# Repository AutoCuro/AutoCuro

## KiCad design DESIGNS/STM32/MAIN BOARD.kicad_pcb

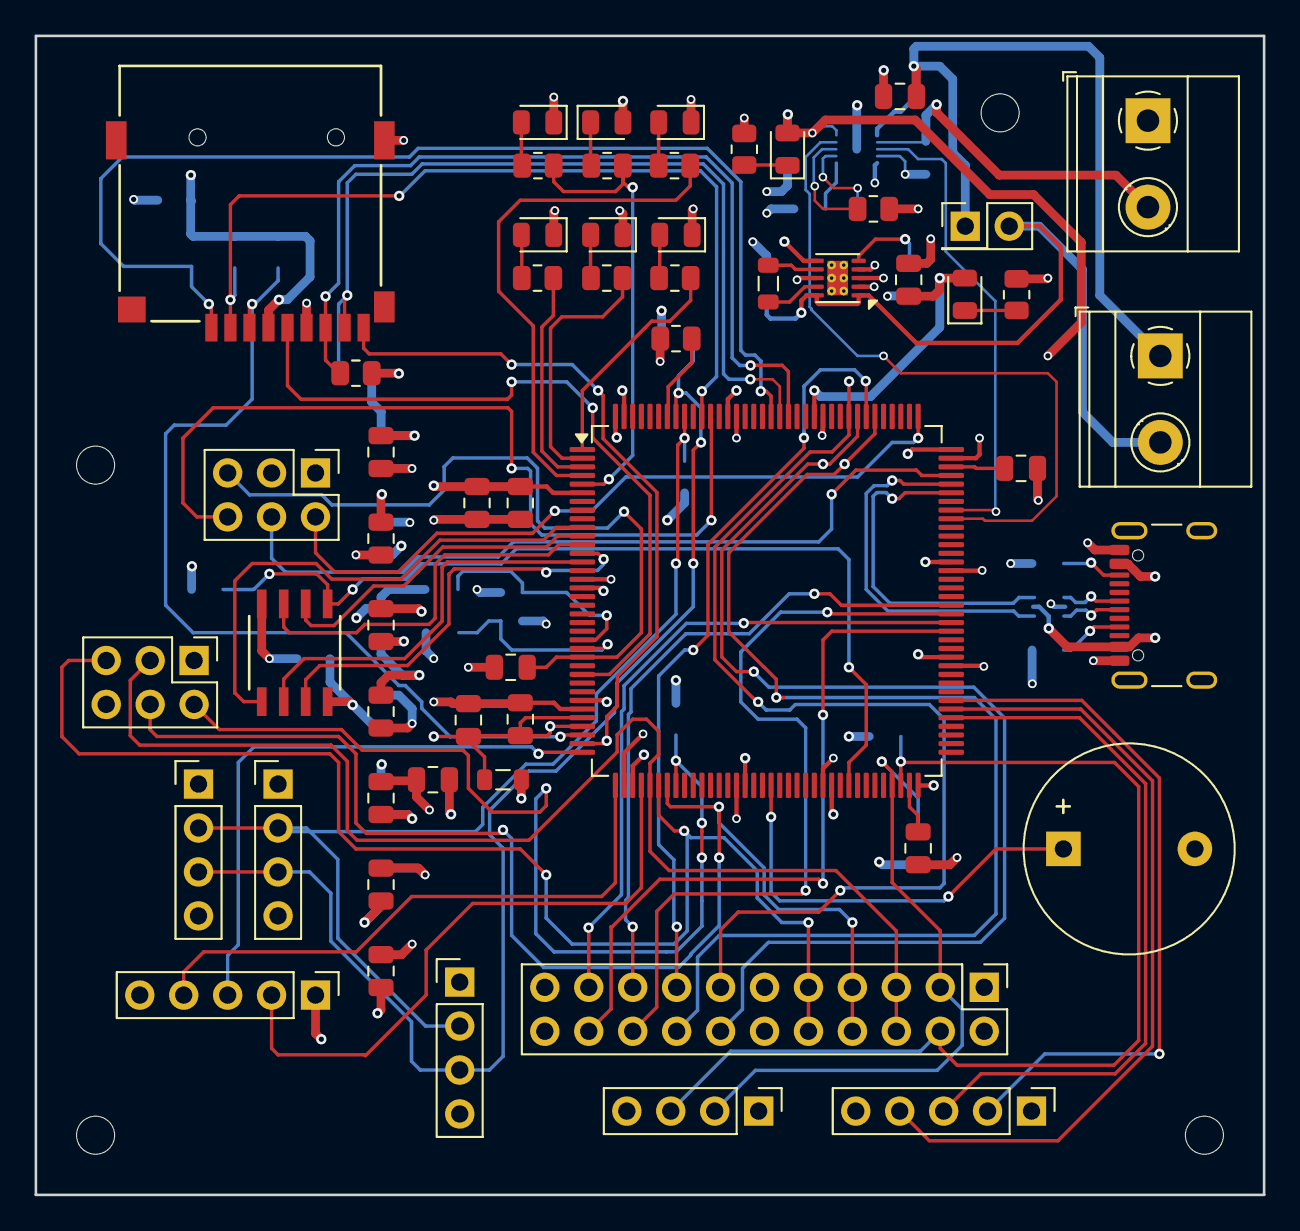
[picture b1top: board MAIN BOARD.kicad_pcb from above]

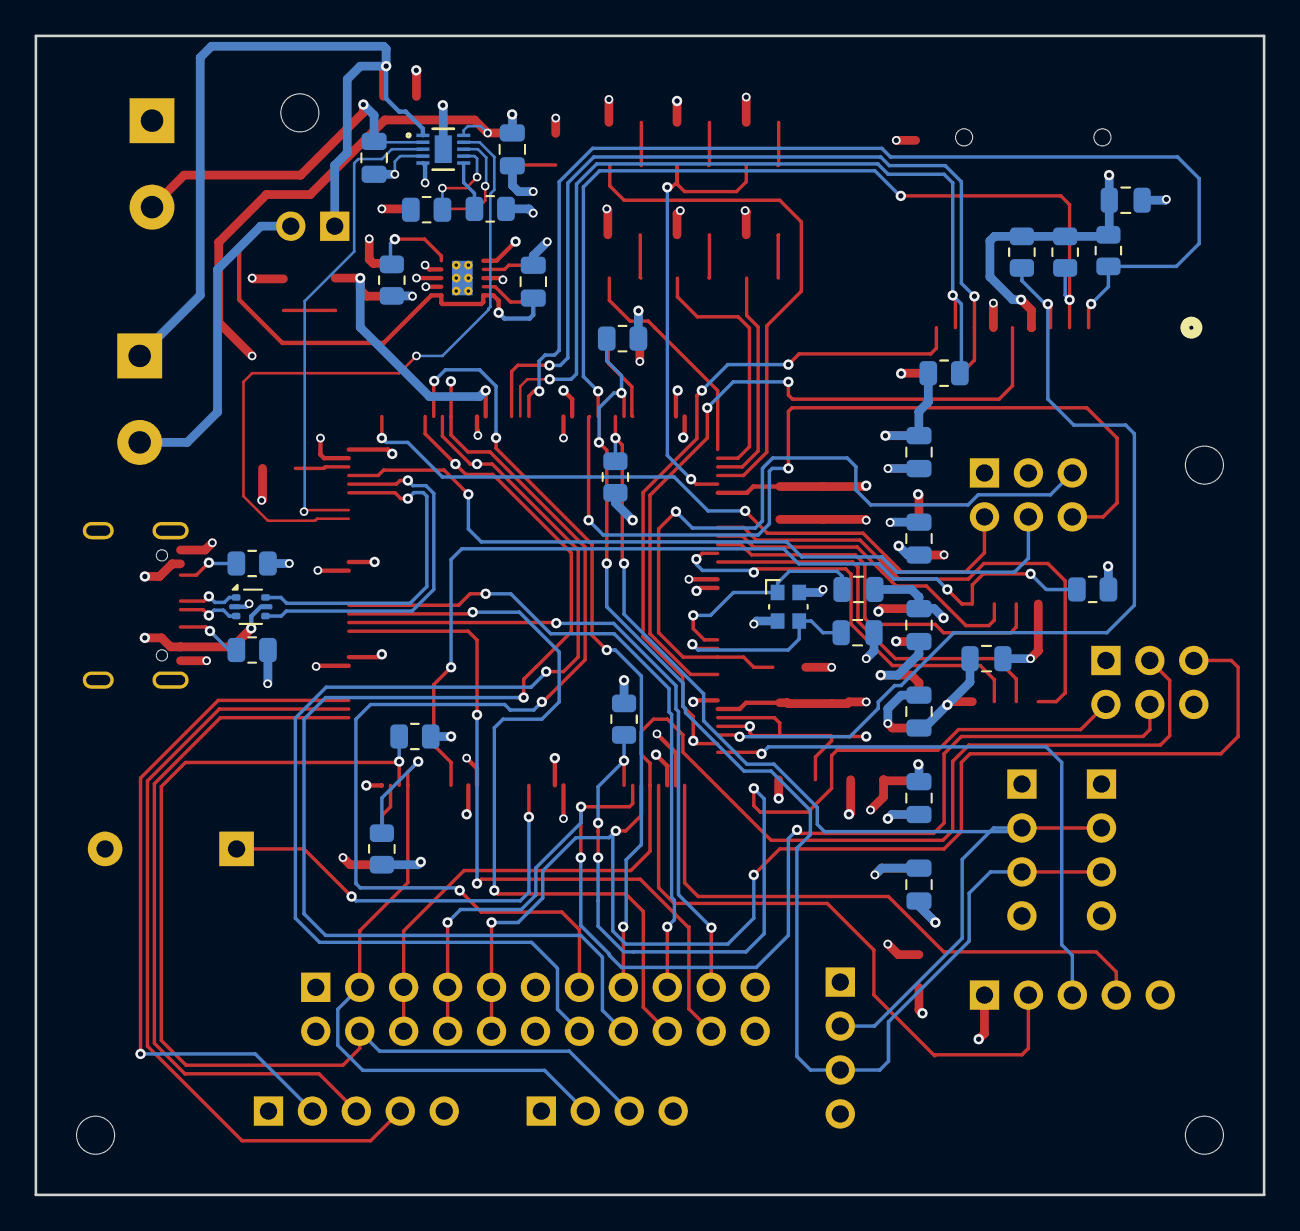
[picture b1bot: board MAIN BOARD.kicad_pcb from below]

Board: 4 copper layers, 71.0 x 67.0 mm, 91 parts (31 on the bottom side), 79 nets.

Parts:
BZ1: Buzzer; Buzzer_12x9.5RM7.6
C1, C28, C29: 10u; C_0805_2012Metric
C2, C3, C4, C5, C6, C7, C11, C13, C14, C15, C16, C17, C18, C19, C20, C23: 100n; C_0805_2012Metric
C8, C9, C12, C26, C27: 1u; C_0805_2012Metric
C10: 10n; C_0805_2012Metric
C21, C22: ??; C_0805_2012Metric
C24, C25: 2u2; C_0805_2012Metric
C30: 22u; C_0805_2012Metric
D1: SD_LED; LED_0805_2012Metric
D2: FLIGHT_LED; LED_0805_2012Metric
D3: SENSOR_LED; LED_0805_2012Metric
D4: RADIO_LED; LED_0805_2012Metric
D5: BAT_GRN_LED; LED_0805_2012Metric
D6: BAT_RED_LED; LED_0805_2012Metric
D7: USB_LED; LED_0805_2012Metric
D8: PWR_LED; LED_0805_2012Metric
FB1: 120R; L_0805_2012Metric
H1, H2, H3, H4: MountingHole; MountingHole_2.2mm_M2
J1: Micro_SD_Card_Det1; CONN9_MSD-1_CUD
J2, J3, J4: I2C1; PinHeader_1x04_P2.54mm_Vertical
J5: I2C2; PinHeader_1x04_P2.54mm_Vertical
J6: SWD; PinHeader_2x03_P2.54mm_Vertical
J7: GPIO; PinHeader_2x11_P2.54mm_Vertical
J8: SPI; PinHeader_2x03_P2.54mm_Vertical
J9: USART1; PinHeader_1x05_P2.54mm_Vertical
J10: USART2; PinHeader_1x05_P2.54mm_Vertical
J11: USB_C_Plug_USB2.0; USB_C_Receptacle_GCT_USB4105-xx-A_16P_TopMnt_Horizontal
J12: BAT_TERM; TerminalBlock_Phoenix_MKDS-1,5-2_1x02_P5.00mm_Horizontal
J13: SW_TERM; TerminalBlock_Phoenix_MKDS-1,5-2_1x02_P5.00mm_Horizontal
JP1: Open; PinHeader_2x01_P2.54mm_Vertical
L1: 2u2; L_0805_2012Metric
R1, R2, R3, R5, R6, R14, R15, R16, R17, R18, R19, R23: 10k; R_0805_2012Metric
R7: 100k; R_0805_2012Metric
R8, R9, R10, R11, R12, R13, R22, R25: ??; R_0805_2012Metric
R20, R21: 5k1; R_0805_2012Metric
R24: 13k; R_0805_2012Metric
R26: 600R; R_0805_2012Metric
R27: 16k2; R_0805_2012Metric
U1: STM32H7A3ZITx; LQFP-144_20x20mm_P0.5mm
U2: IS66WVS4M8BLL-104NLI; SOIC8_150MIL_N_ISI-M
U3: TPS63900; WSON-10-1EP_2.5x2.5mm_P0.5mm_EP1.2x2mm_ThermalVias
U4: BQ25185DLHR; WSON10_DLH_TEX-M
U5: USBLC6-2P6; SOT-666
Y1: 16Mhz; Crystal_SMD_Abracon_ABM10-4Pin_2.5x2.0mm

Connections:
+3V3: C1.1, C2.1, C3.1, C4.1, C5.1, C6.1, C7.1, C8.1, C11.2, C12.2, C13.2, C14.2, C15.2, C16.2, C17.2, C18.2, C19.2, C23.1, C30.1, D5.2 (A), D8.2 (A), FB1.2, J1.4 (VDD), J2.1, J3.1, J4.1, J5.1, J6.1, J7.2, J7.12, J7.22, J8.1, J9.1, J10.1, R1.2, R2.2, R3.2, R5.2, R6.2, R14.2, R15.1, R16.2, R17.1, R18.1, R19.2, U1.6 (VBAT), U1.17 (VDD), U1.30 (VDD), U1.39 (VDD), U1.52 (VDD), U1.62 (VDD), U1.72 (VDD), U1.84 (VDD), U1.95 (VDD33_USB), U1.108 (VDD), U1.121 (VDDMMC), U1.131 (VDD), U1.143 (PDR_ON), U1.144 (VDD), U2.8 (VDD), U3.6 (VOUT)
+3V3A: C9.1, C10.1, FB1.1, U1.32 (VREF+), U1.33 (VDDA)
/BOOT0: R7.2, U1.138 (BOOT0)
/GPIO_1: J7.13, U1.117 (PD3)
/GPIO_2: J7.14, U1.116 (PD2)
/GPIO_3: J7.15, U1.115 (PD1)
/GPIO_4: J7.16, U1.114 (PD0)
/GPIO_5: J7.17, U1.90 (PG5)
/GPIO_6: J7.18, U1.89 (PG4)
/GPIO_7: J7.19, U1.88 (PG3)
/GPIO_8: J7.20, U1.87 (PG2)
/LED_BAT_AMT: R12.1, R13.1, U1.5 (PE6)
/LED_FLIGHT: R9.1, U1.4 (PE5)
/LED_RADIO: R11.1, U1.2 (PE3)
/LED_SD: R8.2, U1.3 (PE4)
/LED_SENSOR: R10.1, U1.1 (PE2)
/MISO: J7.9, J7.10, J8.5, U1.42 (PA6)
/MOSI: J7.7, J7.8, J8.4, U1.43 (PA7)
/NRST: C20.2, J6.5, U1.25 (NRST)
/PSRAM_CLK: U1.14 (PF4), U2.6 (CLK)
/PSRAM_D0: U1.10 (PF0), U2.5 (SI/SIO0)
/PSRAM_D1: U1.11 (PF1), U2.2 (SO/SIO1)
/PSRAM_D2: U1.12 (PF2), U2.3 (SIO2)
/PSRAM_D3: U1.13 (PF3), U2.7 (SIO3)
/PSRAM_NCS: R19.1, U1.64 (PE11), U2.1 (NCS)
/Power/VCOMB_1: C28.1, J13.1, JP1.1 (A), U4.1 (SYS)
/Power/VCOMB_2: C29.1, J13.2, JP1.2 (B), U3.1 (EN), U3.10 (VIN)
/RCC_IN: C21.1, U1.23 (PH0), Y1.1
/RCC_OUT: C22.1, U1.24 (PH1), Y1.3
/SCLK: J7.5, J7.6, J8.3, U1.41 (PA5)
/SCL_1: J2.2, J3.2, J4.2, R14.1, U1.136 (PB6)
/SCL_2: J5.2, J7.3, R16.1, U1.69 (PB10)
/SDA_1: J2.3, J3.3, J4.3, R15.2, U1.137 (PB7)
/SDA_2: J5.3, J7.4, R17.2, U1.70 (PB11)
/SD_CLK: J1.5 (CLK), U1.27 (PC1)
/SD_CMD: J1.3 (CMD), R1.1, U1.34 (PA0)
/SD_D0: J1.7 (DAT0), R6.1, U1.124 (PG9)
/SD_D1: J1.8 (DAT1), R5.1, U1.125 (PG10)
/SD_D2: J1.1 (DAT2), R3.1, U1.126 (PG11)
/SD_D3: J1.2 (DAT3/CD), R2.1, U1.134 (PB4)
/SD_DETECT: J1.9 (DET), U1.35 (PA1)
/SPI_NCS: J8.2, R18.2, U1.44 (PC4)
/SWDCK: J6.2, U1.109 (PA14)
/SWDIO: J6.4, U1.105 (PA13)
/SWO: J6.6, U1.133 (PB3)
/USART1_CK: J9.2, U1.40 (PA4)
/USART1_RX: J9.4, U1.37 (PA3)
/USART1_TX: J9.3, U1.36 (PA2)
/USART2_CK: J10.2, U1.79 (PD10)
/USART2_RX: J10.4, U1.78 (PD9)
/USART2_TX: J10.3, U1.77 (PD8)
/USB_D+: U1.104 (PA12), U5.4 (I/O2)
/USB_D-: U1.103 (PA11), U5.6 (I/O1)
/USB_ESD_D+: J11.A6 (D+), U5.3 (I/O2)
/USB_ESD_D-: J11.A7 (D-), U5.1 (I/O1)
BAT_LED1: U1.100 (PA8), U4.9 (STAT1)
BAT_LED2: U1.101 (PA9), U4.3 (STAT2)
GND: BZ1.2 (-), C1.2, C2.2, C3.2, C4.2, C5.2, C6.2, C7.2, C8.2, C9.2, C10.2, C11.1, C12.1, C13.1, C14.1, C15.1, C16.1, C17.1, C18.1, C19.1, C20.1, C21.2, C22.2, C23.2, C24.1, C25.1, C26.2, C27.2, C28.2, C29.2, C30.2, D1.1 (K), D2.1 (K), D3.1 (K), D4.1 (K), D6.1 (K), J1.6 (VSS), J1.10 (SHIELD), J2.4, J3.4, J4.4, J5.4, J6.3, J7.1, J7.11, J7.21, J8.6, J9.5, J10.5, J11.A1 (GND), J11.A12 (GND), J11.B1 (GND), J11.B12 (GND), J12.1, R7.1, R20.2, R21.2, R22.1, R23.2, R24.1, R25.1, R26.1, R27.2, U1.16 (VSS), U1.31 (VSSA), U1.38 (VSS), U1.51 (VSS), U1.61 (VSS), U1.83 (VSS), U1.94 (VSS), U1.107 (VSS), U1.120 (VSS), U1.130 (VSS), U2.4 (VSS), U3.2 (SEL), U3.3 (CFG1), U3.4 (CFG2), U3.8 (GND), U3.11 (GND), U4.4 (/CE), U4.5 (GND), U4.11 (EPAD), U5.2 (GND), Y1.2, Y1.4
unnamed: BZ1.1 (+), U1.55 (PF15)
unnamed: C24.2, U1.71 (VCAP)
unnamed: C25.2, U1.106 (VCAP)
unnamed: D1.2 (A), R8.1
unnamed: D2.2 (A), R9.2
unnamed: D3.2 (A), R10.2
unnamed: D4.2 (A), R11.2
unnamed: D5.1 (K), R12.2
unnamed: D6.2 (A), R13.2
unnamed: D7.1 (K), R22.2
unnamed: D8.1 (K), R25.2
unnamed: J11.A5 (CC), R20.1
unnamed: J11.B5 (VCONN), R21.1
unnamed: R27.1, U3.5 (CFG3)
unnamed: L1.1, U3.9 (LX1)
unnamed: L1.2, U3.7 (LX2)
unnamed: R24.2, U4.7 (ILIM/VSET)
unnamed: R26.2, U4.8 (ISET)
unnamed: R23.1, U4.6 (TS/MR)
VBAT: C27.1, J12.2, U4.2 (BAT)
VBUS: C26.1, D7.2 (A), J11.A4 (VBUS), J11.A9 (VBUS), J11.B4 (VBUS), J11.B9 (VBUS), U4.10 (VIN), U5.5 (VBUS)
